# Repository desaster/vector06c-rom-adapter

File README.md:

# 2KB ROM Adapter for Vector-06C

To attach a 2KB rom to Vector-06c, normally you'd need to cut some traces and
add jumper wires. This mod attempts to eliminate the need to cut traces, and
minimizes the number of external wires.

Status: **~~UNTESTED~~, PROBABLY DANGEROUS ⚠️**

## How to build

1. Replace D9 on the V06C with a good dual wipe socket. Be careful, Vector-06C is delicate.
2. Add legs to the adapter board. Recommended to use thiner legs from "long leg female pin headers" to prevent damage to the socket.
3. Solder the two jumper wires of appropriate length to the adapter board, and connect them to the D1 chip on the Vector-06C.
4. Solder a double wipe socket to the adapter.
5. Add 2KB ROM chip to the adapter and enjoy.

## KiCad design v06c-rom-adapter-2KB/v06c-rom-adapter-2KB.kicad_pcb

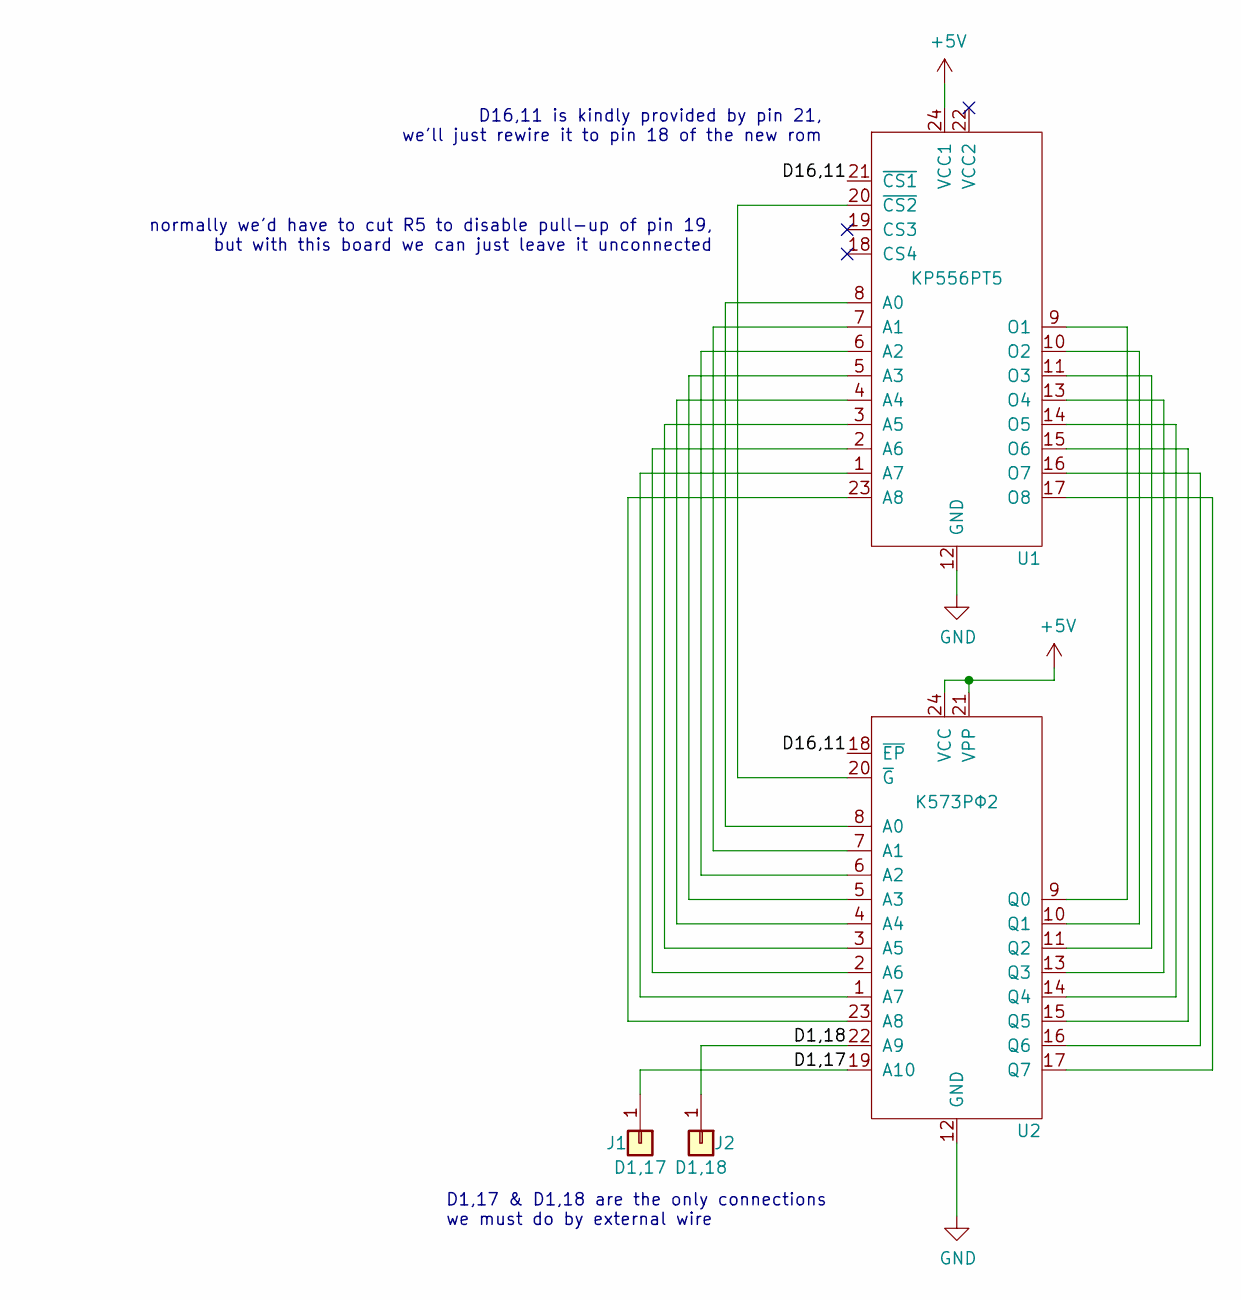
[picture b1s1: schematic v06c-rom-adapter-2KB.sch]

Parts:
J1: D1,17; PinHeader_1x01_P2.54mm_Vertical
J2: D1,18; PinHeader_1x01_P2.54mm_Vertical
U1: KP556PT5; DIP-24_W15.24mm_nosilk
U2: K573PФ2; DIP-24_W15.24mm_nosilk

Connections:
+5V: U1.24 (VCC1), U2.21 (VPP), U2.24 (VCC)
/D1,17: J1.1, U2.19 (A10)
/D1,18: J2.1, U2.22 (A9)
/D16,11: U1.21 (~CS1), U2.18 (~EP)
GND: U1.12 (GND), U2.12 (GND)
unnamed: U1.1 (A7), U2.1 (A7)
unnamed: U1.2 (A6), U2.2 (A6)
unnamed: U1.3 (A5), U2.3 (A5)
unnamed: U1.4 (A4), U2.4 (A4)
unnamed: U1.5 (A3), U2.5 (A3)
unnamed: U1.6 (A2), U2.6 (A2)
unnamed: U1.7 (A1), U2.7 (A1)
unnamed: U1.8 (A0), U2.8 (A0)
unnamed: U1.9 (O1), U2.9 (Q0)
unnamed: U1.10 (O2), U2.10 (Q1)
unnamed: U1.11 (O3), U2.11 (Q2)
unnamed: U1.13 (O4), U2.13 (Q3)
unnamed: U1.14 (O5), U2.14 (Q4)
unnamed: U1.15 (O6), U2.15 (Q5)
unnamed: U1.16 (O7), U2.16 (Q6)
unnamed: U1.17 (O8), U2.17 (Q7)
unnamed: U1.20 (~CS2), U2.20 (~G)
unnamed: U1.23 (A8), U2.23 (A8)

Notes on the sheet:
D16,11 is kindly provided by pin 21, we'll just rewire it to pin 18 of the new rom
D1,17 & D1,18 are the only connections we must do by external wire
normally we'd have to cut R5 to disable pull-up of pin 19, but with this board we can just leave it unconnected

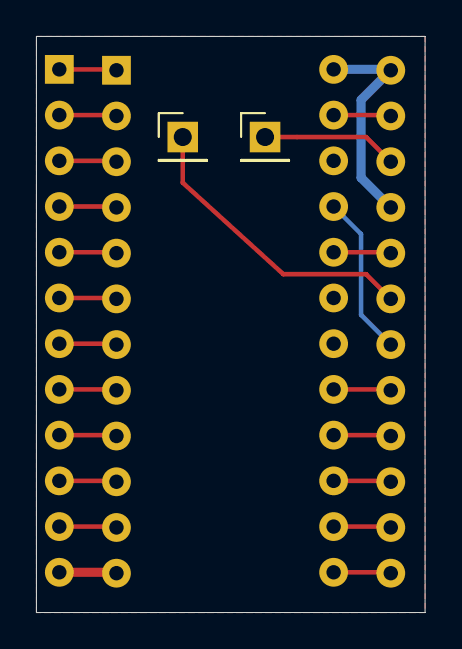
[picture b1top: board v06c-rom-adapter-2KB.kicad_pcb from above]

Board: 2 copper layers, 21.6 x 32.0 mm, 4 parts (0 on the bottom side), 23 nets.

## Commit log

2020-06-24 fix image link
2020-06-24 add boot_change.pdf
